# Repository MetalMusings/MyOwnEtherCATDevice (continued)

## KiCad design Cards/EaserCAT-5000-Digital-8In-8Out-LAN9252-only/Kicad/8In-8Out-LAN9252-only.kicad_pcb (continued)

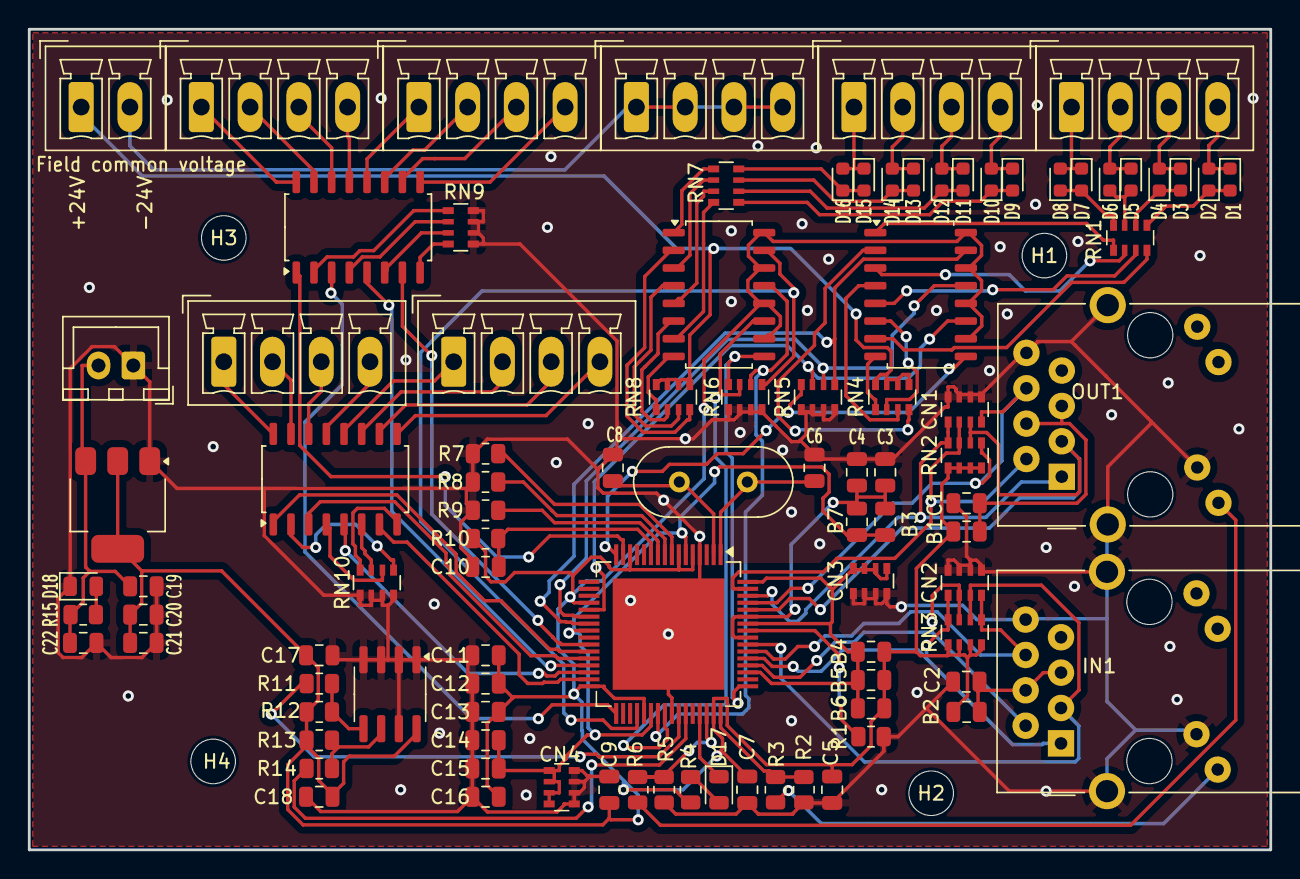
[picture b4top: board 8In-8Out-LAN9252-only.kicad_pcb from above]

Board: 2 copper layers, 89.2 x 58.9 mm, 99 parts (0 on the bottom side), 108 nets.

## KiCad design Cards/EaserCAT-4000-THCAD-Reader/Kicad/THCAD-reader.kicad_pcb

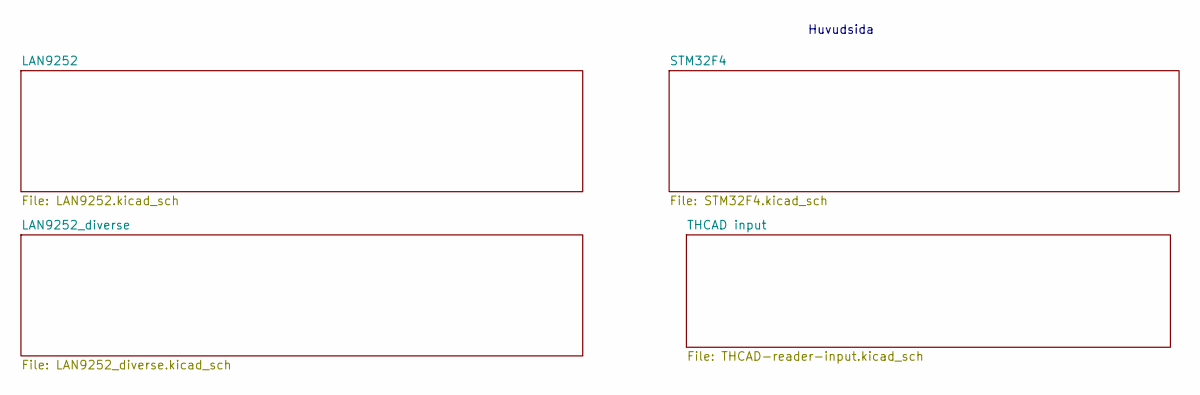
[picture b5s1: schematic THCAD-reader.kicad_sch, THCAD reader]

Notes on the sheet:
Huvudsida

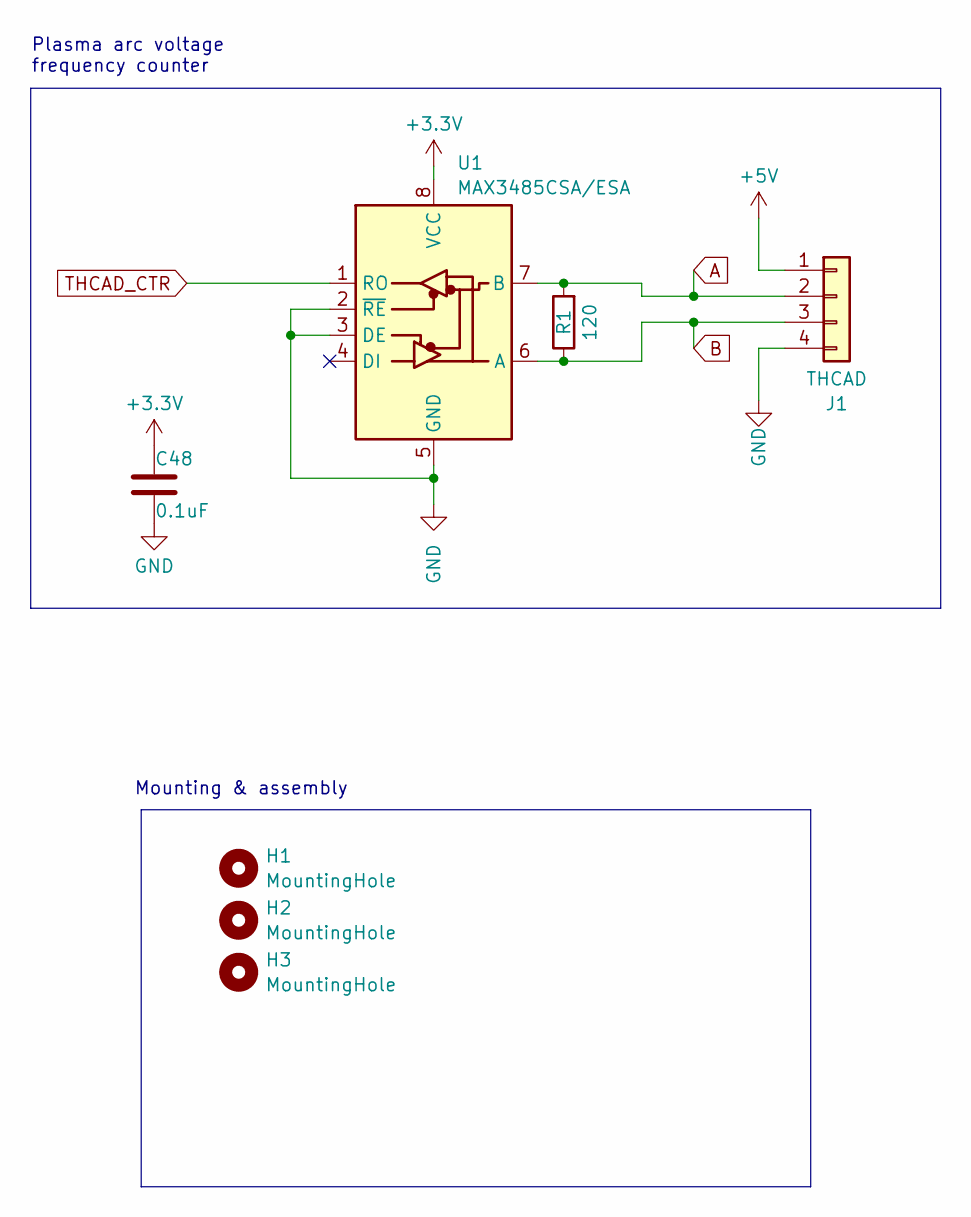
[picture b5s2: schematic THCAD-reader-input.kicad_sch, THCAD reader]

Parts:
C48: 0.1uF; C_0805_2012Metric
H1, H2, H3: MountingHole; MountingHole_3.2mm_M3
J1: THCAD; PhoenixContact_MCV_1,5_4-G-3.5_1x04_P3.50mm_Vertical
R1: 120; R_0805_2012Metric
U1: MAX3485CSA/ESA; SO-8_3.9x4.9mm_P1.27mm

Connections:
+3.3V: C48.1, U1.8 (VCC); also elsewhere on the board
+5V: J1.1; also elsewhere on the board
GND: C48.2, J1.4, U1.2 (~RE), U1.3 (DE), U1.5 (GND); also elsewhere on the board
unnamed: J1.2, R1.2, U1.7 (B)
unnamed: J1.3, R1.1, U1.6 (A)
THCAD_CTR: U1.1 (RO); also elsewhere on the board

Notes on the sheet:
Plasma arc voltage frequency counter
Mounting & assembly

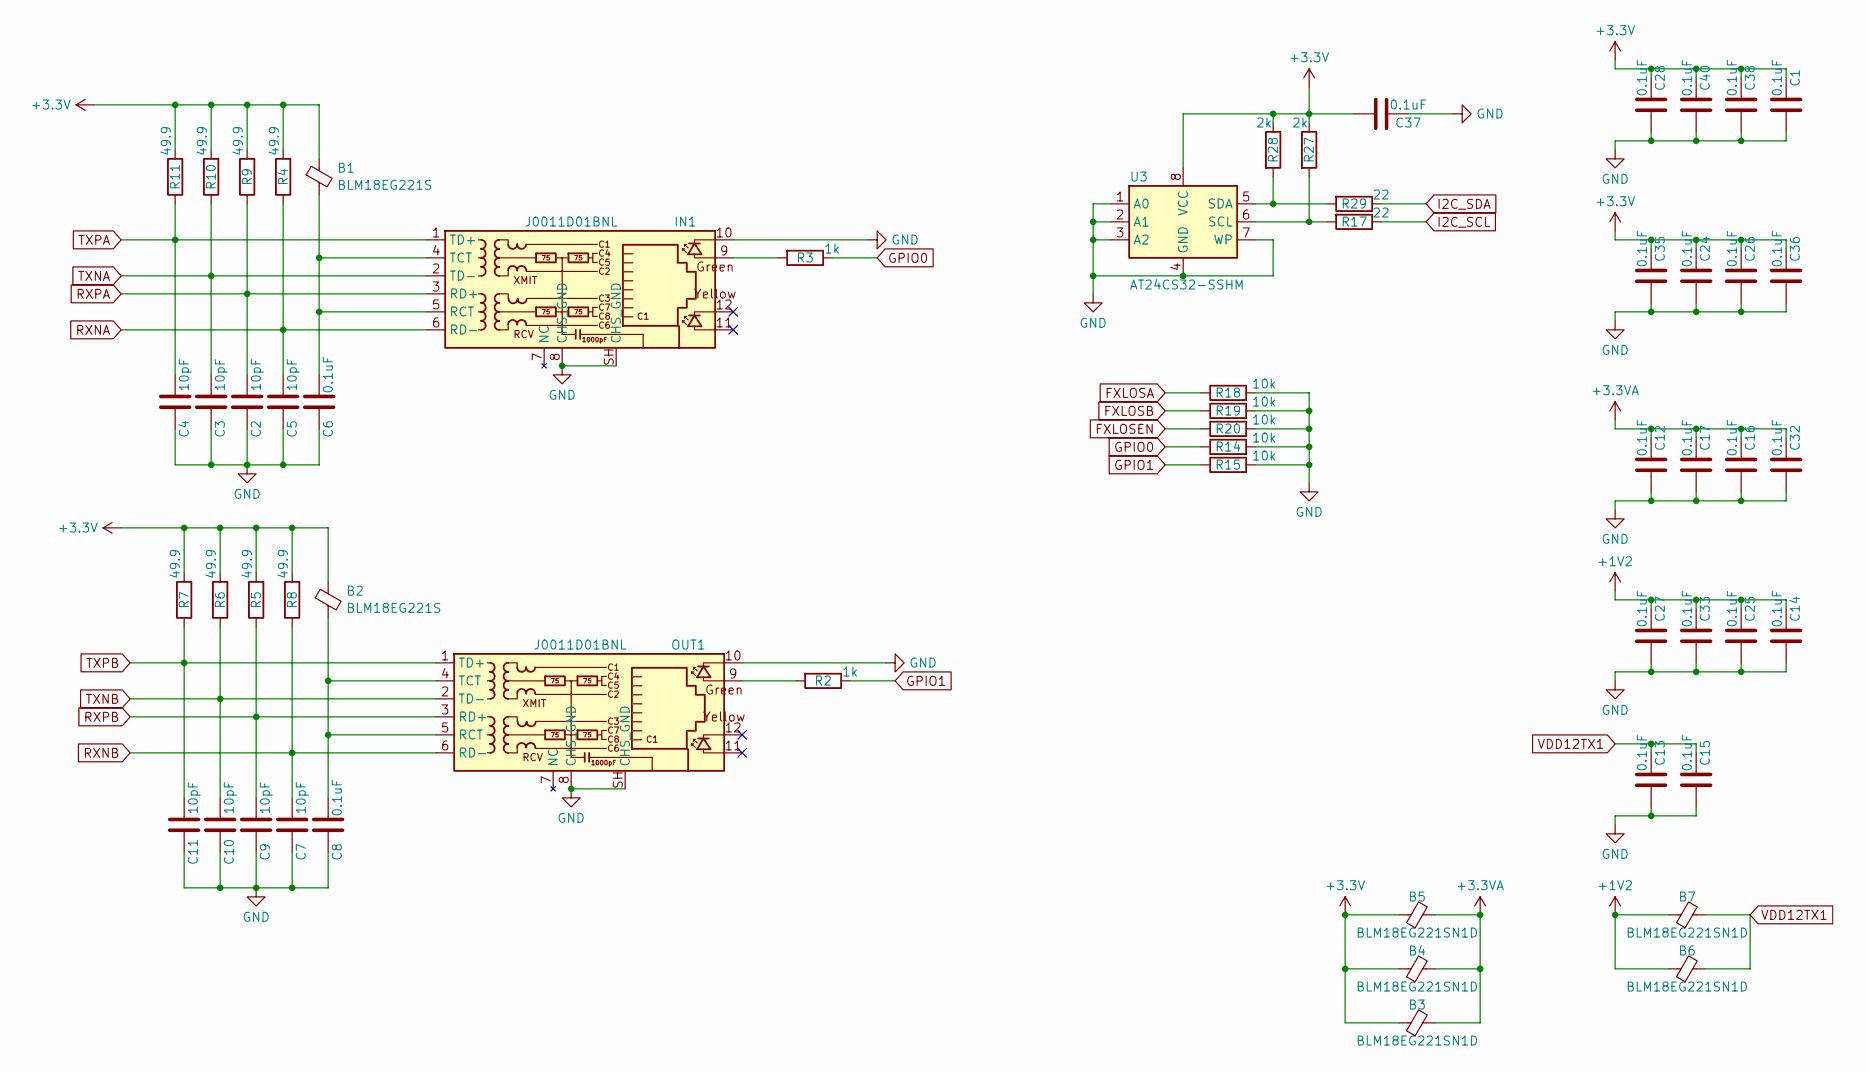
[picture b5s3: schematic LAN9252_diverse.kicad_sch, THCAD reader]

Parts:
B1, B2: BLM18EG221S; C_0805_2012Metric
B3, B4, B5, B6, B7: BLM18EG221SN1D; C_0805_2012Metric
C1, C6, C8, C12, C13, C14, C15, C16, C17, C24, C25, C26, C27, C28, C32, C33, C35, C36, C37, C38, C40: 0.1uF; C_0805_2012Metric
C2, C3, C4, C5, C7, C9, C10, C11: 10pF; C_0805_2012Metric
IN1: J0011D01BNL; PulseJack JB0011D01BNL
OUT1: J0011D01BNL; PulseJack JB0011D01BNL
R2, R3: 1k; R_0805_2012Metric
R4, R5, R6, R7, R8, R9, R10, R11: 49.9; R_0805_2012Metric
R14, R15, R18, R19, R20: 10k; R_0805_2012Metric
R17, R29: 22; R_0805_2012Metric
R27, R28: 2k; R_0805_2012Metric
U3: AT24CS32-SSHM; SOIC-8_3.9x4.9mm_P1.27mm

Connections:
+1V2: B6.1, B7.1, C14.1, C25.1, C27.1, C33.1; also elsewhere on the board
+3.3V: B1.1, B2.1, B3.1, B4.1, B5.1, C1.1, C24.1, C26.1, C28.1, C35.1, C36.1, C37.2, C38.1, C40.1, R4.2, R5.2, R6.2, R7.2, R8.2, R9.2, R10.2, R11.2, R27.1, R28.1, U3.8 (VCC); also elsewhere on the board
+3.3VA: B3.2, B4.2, B5.2, C12.1, C16.1, C17.1, C32.1; also elsewhere on the board
FXLOSA: R18.1; also elsewhere on the board
FXLOSB: R19.1; also elsewhere on the board
FXLOSEN: R20.1; also elsewhere on the board
GND: C1.2, C2.1, C3.1, C4.1, C5.1, C6.1, C7.1, C8.1, C9.1, C10.1, C11.1, C12.2, C13.2, C14.2, C15.2, C16.2, C17.2, C24.2, C25.2, C26.2, C27.2, C28.2, C32.2, C33.2, C35.2, C36.2, C37.1, C38.2, C40.2, IN1.8 (CHS_GND), IN1.10, IN1.SH (CHS_GND), OUT1.8 (CHS_GND), OUT1.10, OUT1.SH (CHS_GND), R14.2, R15.2, R18.2, R19.2, R20.2, U3.1 (A0), U3.2 (A1), U3.3 (A2), U3.4 (GND), U3.7 (WP); also elsewhere on the board
GPIO0: R3.1, R14.1; also elsewhere on the board
GPIO1: R2.1, R15.1; also elsewhere on the board
I2C_SCL: R17.1; also elsewhere on the board
I2C_SDA: R29.1; also elsewhere on the board
unnamed: IN1.9, R3.2
unnamed: B1.2, C6.2, IN1.4 (TCT), IN1.5 (RCT)
unnamed: OUT1.9, R2.2
unnamed: B2.2, C8.2, OUT1.4 (TCT), OUT1.5 (RCT)
unnamed: R17.2, R27.2, U3.6 (SCL)
unnamed: R28.2, R29.2, U3.5 (SDA)
RXNA: C5.2, IN1.6 (RD-), R4.1; also elsewhere on the board
RXNB: C7.2, OUT1.6 (RD-), R8.1; also elsewhere on the board
RXPA: C2.2, IN1.3 (RD+), R9.1; also elsewhere on the board
RXPB: C9.2, OUT1.3 (RD+), R5.1; also elsewhere on the board
TXNA: C3.2, IN1.2 (TD-), R10.1; also elsewhere on the board
TXNB: C10.2, OUT1.2 (TD-), R6.1; also elsewhere on the board
TXPA: C4.2, IN1.1 (TD+), R11.1; also elsewhere on the board
TXPB: C11.2, OUT1.1 (TD+), R7.1; also elsewhere on the board
VDD12TX1: B6.2, B7.2, C13.1, C15.1; also elsewhere on the board

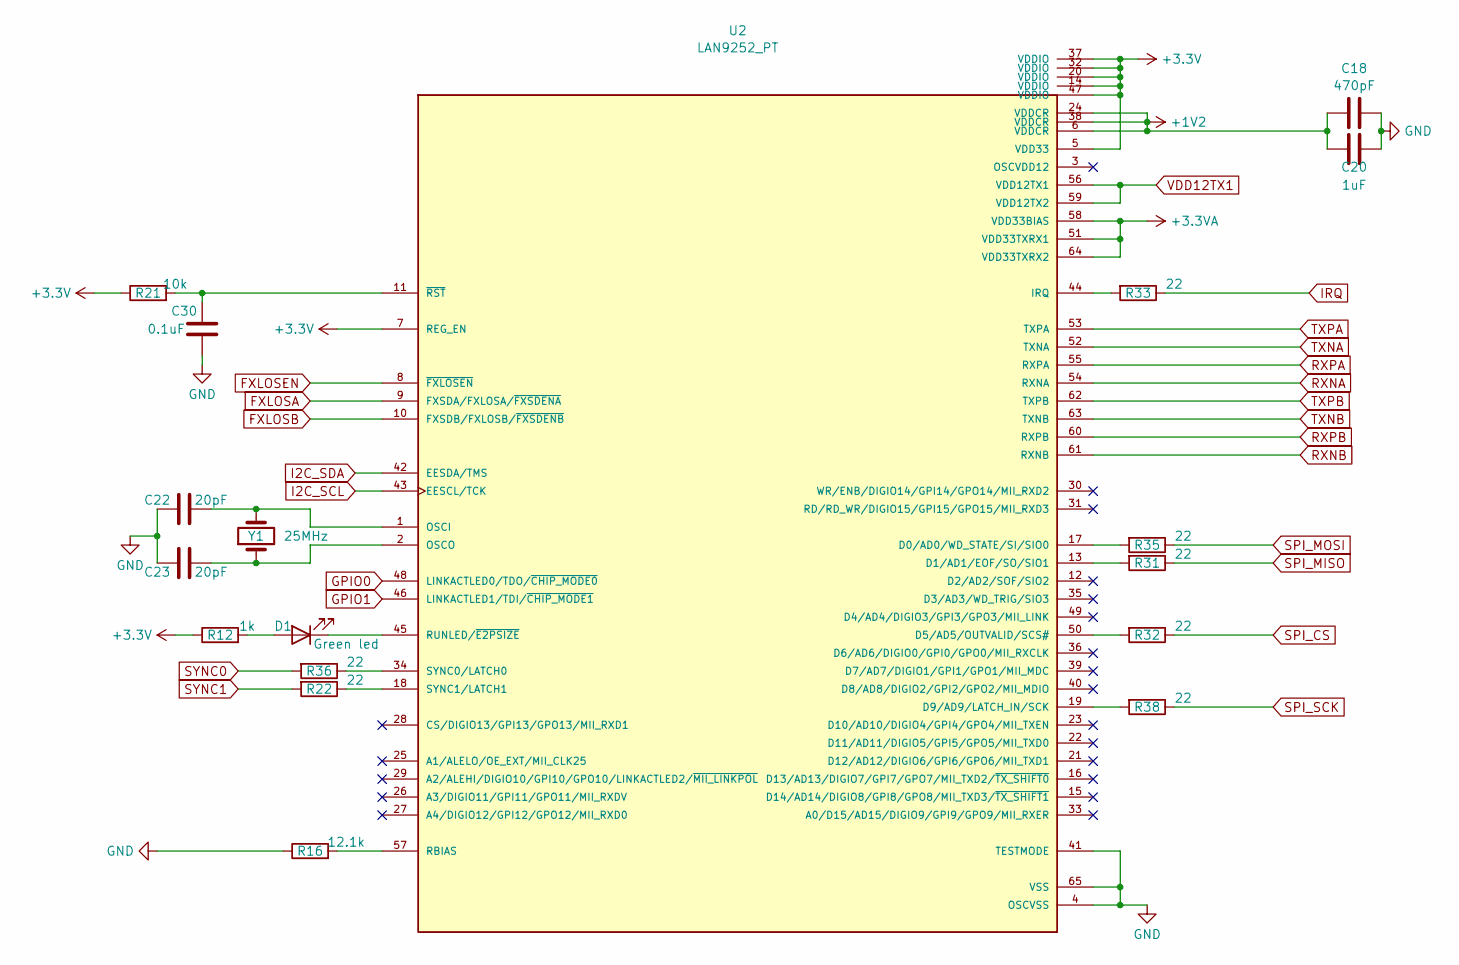
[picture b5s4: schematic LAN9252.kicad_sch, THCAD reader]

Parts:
C18: 470pF; C_0805_2012Metric
C20: 1uF; C_0805_2012Metric
C22, C23: 20pF; C_0805_2012Metric
C30: 0.1uF; C_0805_2012Metric
D1: Green led; LED_0805_2012Metric
R12: 1k; R_0805_2012Metric
R16: 12.1k; R_0805_2012Metric
R21: 10k; R_0805_2012Metric
R22, R31, R32, R33, R35, R36, R38: 22; R_0805_2012Metric
U2: LAN9252_PT; TQFP-64-1EP_10x10mm_P0.5mm_EP8x8mm; PARTREV 04-08-15
Y1: 25MHz; Crystal_HC49-4H_Vertical

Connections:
+1V2: C18.1, C20.1, U2.6 (VDDCR), U2.24 (VDDCR), U2.38 (VDDCR); also elsewhere on the board
+3.3V: R12.1, R21.1, U2.5 (VDD33), U2.7 (REG_EN), U2.14 (VDDIO), U2.20 (VDDIO), U2.32 (VDDIO), U2.37 (VDDIO), U2.47 (VDDIO); also elsewhere on the board
+3.3VA: U2.51 (VDD33TXRX1), U2.58 (VDD33BIAS), U2.64 (VDD33TXRX2); also elsewhere on the board
FXLOSA: U2.9 (FXSDA/FXLOSA/~FXSDENA); also elsewhere on the board
FXLOSB: U2.10 (FXSDB/FXLOSB/~FXSDENB); also elsewhere on the board
FXLOSEN: U2.8 (~FXLOSEN); also elsewhere on the board
GND: C18.2, C20.2, C22.1, C23.1, C30.1, R16.1, U2.4 (OSCVSS), U2.41 (TESTMODE), U2.65 (VSS); also elsewhere on the board
GPIO0: U2.48 (LINKACTLED0/TDO/~CHIP_MODE0); also elsewhere on the board
GPIO1: U2.46 (LINKACTLED1/TDI/~CHIP_MODE1); also elsewhere on the board
I2C_SCL: U2.43 (EESCL/TCK); also elsewhere on the board
I2C_SDA: U2.42 (EESDA/TMS); also elsewhere on the board
IRQ: R33.1; also elsewhere on the board
unnamed: D1.2 (A), R12.2
unnamed: D1.1 (K), U2.45 (RUNLED/~E2PSIZE)
unnamed: R35.2, U2.17 (D0/AD0/WD_STATE/SI/SIO0)
unnamed: R31.2, U2.13 (D1/AD1/EOF/SO/SIO1)
unnamed: R32.2, U2.50 (D5/AD5/OUTVALID/SCS#)
unnamed: R38.2, U2.19 (D9/AD9/LATCH_IN/SCK)
unnamed: R33.2, U2.44 (IRQ)
unnamed: C22.2, U2.1 (OSCI), Y1.2
unnamed: C23.2, U2.2 (OSCO), Y1.1
unnamed: R16.2, U2.57 (RBIAS)
unnamed: R36.1, U2.34 (SYNC0/LATCH0)
unnamed: R22.1, U2.18 (SYNC1/LATCH1)
unnamed: C30.2, R21.2, U2.11 (~RST)
RXNA: U2.54 (RXNA); also elsewhere on the board
RXNB: U2.61 (RXNB); also elsewhere on the board
RXPA: U2.55 (RXPA); also elsewhere on the board
RXPB: U2.60 (RXPB); also elsewhere on the board
SPI_CS: R32.1; also elsewhere on the board
SPI_MISO: R31.1; also elsewhere on the board
SPI_MOSI: R35.1; also elsewhere on the board
SPI_SCK: R38.1; also elsewhere on the board
SYNC0: R36.2; also elsewhere on the board
SYNC1: R22.2; also elsewhere on the board
TXNA: U2.52 (TXNA); also elsewhere on the board
TXNB: U2.63 (TXNB); also elsewhere on the board
TXPA: U2.53 (TXPA); also elsewhere on the board
TXPB: U2.62 (TXPB); also elsewhere on the board
VDD12TX1: U2.56 (VDD12TX1), U2.59 (VDD12TX2); also elsewhere on the board

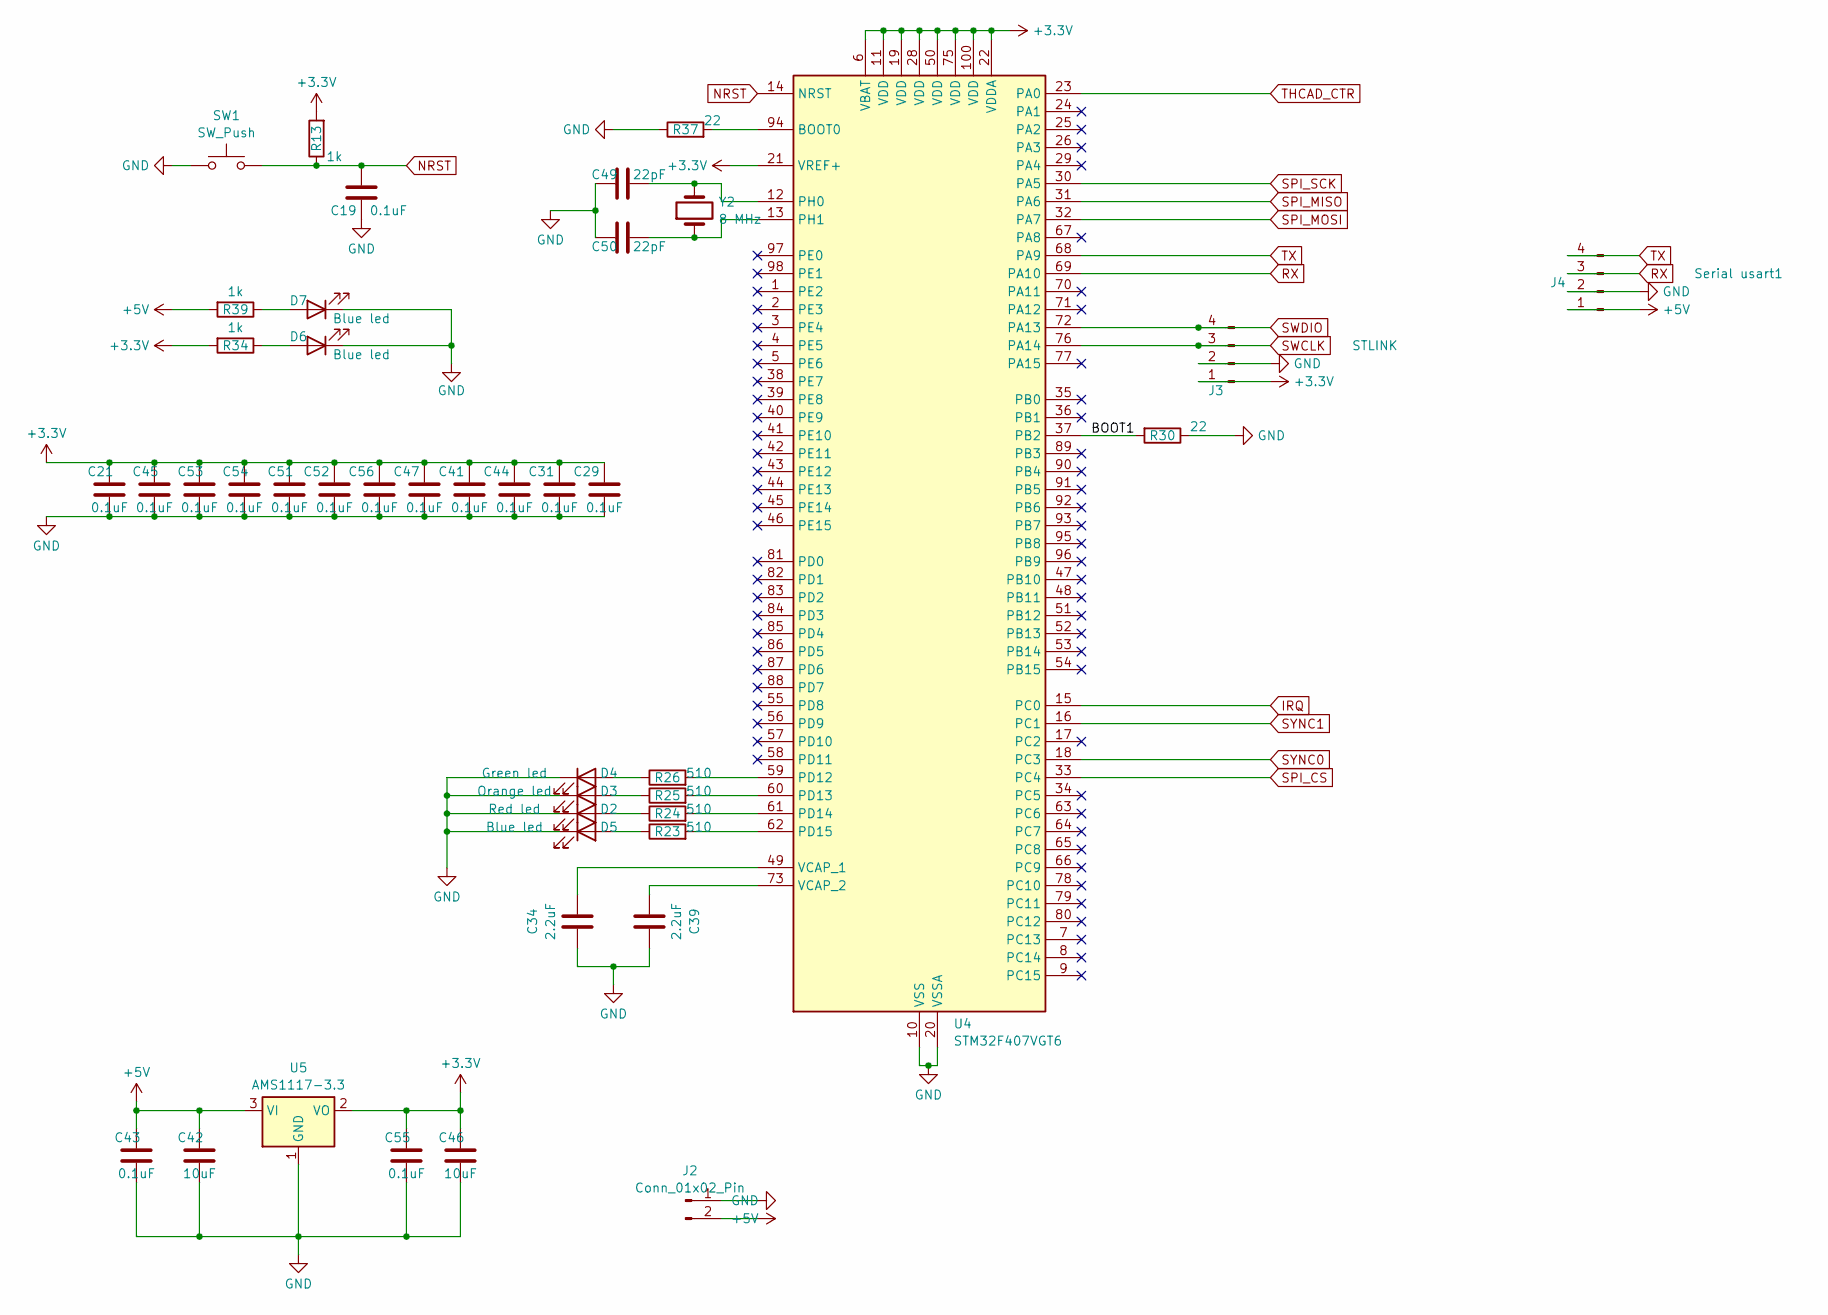
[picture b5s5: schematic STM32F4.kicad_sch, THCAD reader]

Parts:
C19, C21, C29, C31, C41, C43, C44, C45, C47, C51, C52, C53, C54, C55, C56: 0.1uF; C_0805_2012Metric
C34, C39: 2.2uF; C_0805_2012Metric
C42, C46: 10uF; C_0805_2012Metric
C49, C50: 22pF; C_0805_2012Metric
D2: Red led; LED_0805_2012Metric
D3: Orange led; LED_0805_2012Metric
D4: Green led; LED_0805_2012Metric
D5, D6, D7: Blue led; LED_0805_2012Metric
J2: Conn_01x02_Pin; JST_XH_B2B-XH-A_1x02_P2.50mm_Vertical
J3: STLINK; JST_XH_B4B-XH-A_1x04_P2.50mm_Vertical
J4: Serial usart1; JST_XH_B4B-XH-A_1x04_P2.50mm_Vertical
R13, R34, R39: 1k; R_0805_2012Metric
R23, R24, R25, R26: 510; R_0805_2012Metric
R30, R37: 22; R_0805_2012Metric
SW1: SW_Push; SW_Push_1P1T_XKB_TS-1187A
U4: STM32F407VGT6; LQFP-100_14x14mm_P0.5mm
U5: AMS1117-3.3; SOT-223-3_TabPin2
Y2: 8 MHz; Crystal_HC49-4H_Vertical

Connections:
+3.3V: C21.1, C29.1, C31.1, C41.1, C44.1, C45.1, C46.1, C47.1, C51.1, C52.1, C53.1, C54.1, C55.1, C56.1, J3.1, R13.2, R34.2, U4.6 (VBAT), U4.11 (VDD), U4.19 (VDD), U4.21 (VREF+), U4.22 (VDDA), U4.28 (VDD), U4.50 (VDD), U4.75 (VDD), U4.100 (VDD), U5.2 (VO); also elsewhere on the board
+5V: C42.1, C43.1, J2.2, J4.1, R39.2, U5.3 (VI); also elsewhere on the board
/STM32F4/BOOT1: R30.2, U4.37 (PB2)
GND: C19.1, C21.2, C29.2, C31.2, C34.1, C39.1, C41.2, C42.2, C43.2, C44.2, C45.2, C46.2, C47.2, C49.1, C50.1, C51.2, C52.2, C53.2, C54.2, C55.2, C56.2, D2.1 (K), D3.1 (K), D4.1 (K), D5.1 (K), D6.1 (K), D7.1 (K), J2.1, J3.2, J4.2, R30.1, R37.1, SW1.1, U4.10 (VSS), U4.20 (VSSA), U4.27 (VSS), U4.74 (VSS), U4.99 (VSS), U5.1 (GND); also elsewhere on the board
IRQ: U4.15 (PC0); also elsewhere on the board
NRST: C19.2, R13.1, SW1.2, U4.14 (NRST)
unnamed: D2.2 (A), R24.1
unnamed: D3.2 (A), R25.1
unnamed: D4.2 (A), R26.1
unnamed: D5.2 (A), R23.1
unnamed: D6.2 (A), R34.1
unnamed: D7.2 (A), R39.1
unnamed: R37.2, U4.94 (BOOT0)
unnamed: R26.2, U4.59 (PD12)
unnamed: R25.2, U4.60 (PD13)
unnamed: R24.2, U4.61 (PD14)
unnamed: R23.2, U4.62 (PD15)
unnamed: C49.2, U4.12 (PH0), Y2.2
unnamed: C50.2, U4.13 (PH1), Y2.1
unnamed: C34.2, U4.49 (VCAP_1)
unnamed: C39.2, U4.73 (VCAP_2)
RX: J4.3, U4.69 (PA10)
SPI_CS: U4.33 (PC4); also elsewhere on the board
SPI_MISO: U4.31 (PA6); also elsewhere on the board
SPI_MOSI: U4.32 (PA7); also elsewhere on the board
SPI_SCK: U4.30 (PA5); also elsewhere on the board
SWCLK: J3.3, U4.76 (PA14)
SWDIO: J3.4, U4.72 (PA13)
SYNC0: U4.18 (PC3); also elsewhere on the board
SYNC1: U4.16 (PC1); also elsewhere on the board
THCAD_CTR: U4.23 (PA0); also elsewhere on the board
TX: J4.4, U4.68 (PA9)

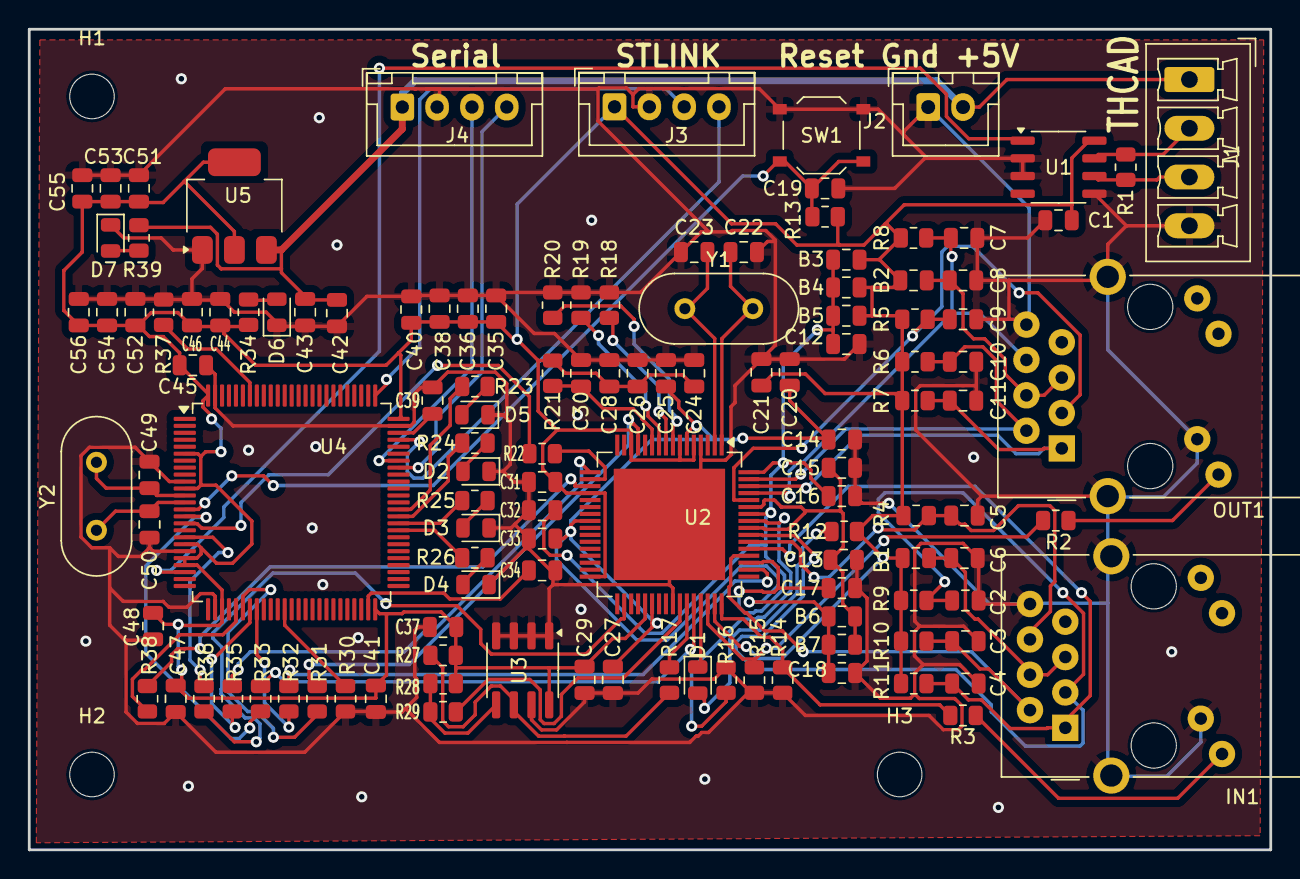
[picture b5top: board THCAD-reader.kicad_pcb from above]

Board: 2 copper layers, 89.2 x 58.9 mm, 126 parts (0 on the bottom side), 71 nets.

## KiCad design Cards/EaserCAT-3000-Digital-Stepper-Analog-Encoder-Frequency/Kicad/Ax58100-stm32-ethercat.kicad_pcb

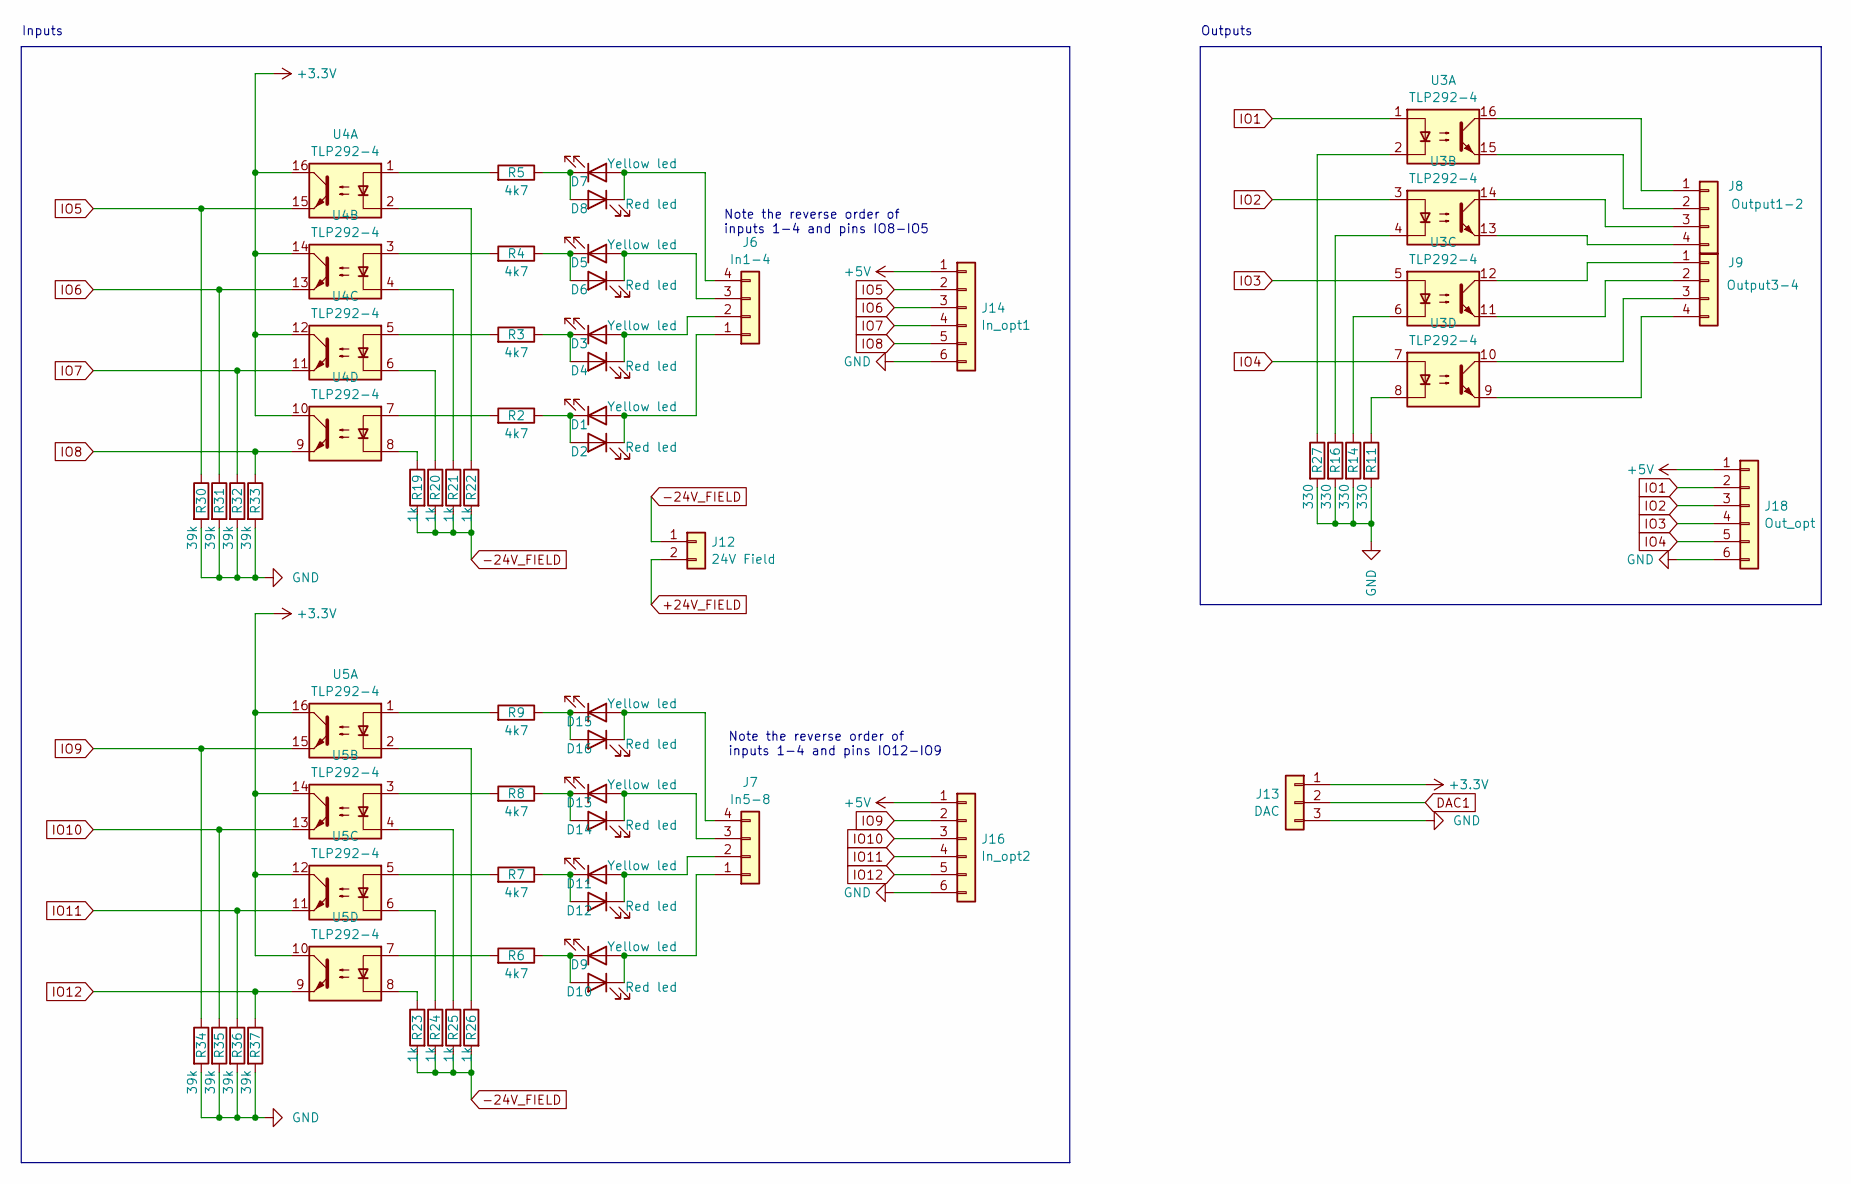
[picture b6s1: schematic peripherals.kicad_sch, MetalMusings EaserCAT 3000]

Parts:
D1, D3, D5, D7, D9, D11, D13, D15: Yellow led; LED_0603_1608Metric
D2, D4, D6, D8, D10, D12, D14, D16: Red led; LED_0603_1608Metric
J6: In1-4; PhoenixContact_MCV_1,5_4-G-3.5_1x04_P3.50mm_Vertical
J7: In5-8; PhoenixContact_MCV_1,5_4-G-3.5_1x04_P3.50mm_Vertical
J8: Output1-2; PhoenixContact_MCV_1,5_4-G-3.5_1x04_P3.50mm_Vertical
J9: Output3-4; PhoenixContact_MCV_1,5_4-G-3.5_1x04_P3.50mm_Vertical
J12: 24V Field; PhoenixContact_MCV_1,5_2-G-3.5_1x02_P3.50mm_Vertical
J13: DAC; PhoenixContact_MCV_1,5_3-G-3.5_1x03_P3.50mm_Vertical
J14: In_opt1; JST_XH_B6B-XH-A_1x06_P2.50mm_Vertical
J16: In_opt2; JST_XH_B6B-XH-A_1x06_P2.50mm_Vertical
J18: Out_opt; JST_XH_B6B-XH-A_1x06_P2.50mm_Vertical
R2, R3, R4, R5, R6, R7, R8, R9: 4k7; R_0603_1608Metric
R11, R14, R16, R27: 330; R_0603_1608Metric
R19, R20, R21, R22, R23, R24, R25, R26: 1k; R_0603_1608Metric
R30, R31, R32, R33, R34, R35, R36, R37: 39k; R_0603_1608Metric
U3, U4, U5: TLP292-4; SOIC-16_4.55x10.3mm_P1.27mm

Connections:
+3.3V: J13.1, U4.10, U4.12, U4.14, U4.16, U5.10, U5.12, U5.14, U5.16; also elsewhere on the board
+5V: J14.1, J16.1, J18.1; also elsewhere on the board
+24V_FIELD: J12.2
-24V_FIELD: J12.1, R19.2, R20.2, R21.2, R22.2, R23.2, R24.2, R25.2, R26.2
DAC1: J13.2; also elsewhere on the board
GND: J13.3, J14.6, J16.6, J18.6, R11.2, R14.2, R16.2, R27.2, R30.2, R31.2, R32.2, R33.2, R34.2, R35.2, R36.2, R37.2; also elsewhere on the board
IO1: J18.2, U3.1; also elsewhere on the board
IO2: J18.3, U3.3; also elsewhere on the board
IO3: J18.4, U3.5; also elsewhere on the board
IO4: J18.5, U3.7; also elsewhere on the board
IO5: J14.2, R30.1, U4.15; also elsewhere on the board
IO6: J14.3, R31.1, U4.13; also elsewhere on the board
IO7: J14.4, R32.1, U4.11; also elsewhere on the board
IO8: J14.5, R33.1, U4.9; also elsewhere on the board
IO9: J16.2, R34.1, U5.15; also elsewhere on the board
IO10: J16.3, R35.1, U5.13; also elsewhere on the board
IO11: J16.4, R36.1, U5.11; also elsewhere on the board
IO12: J16.5, R37.1, U5.9; also elsewhere on the board
unnamed: D1.2 (A), D2.1 (K), J6.1
unnamed: D1.1 (K), D2.2 (A), R2.1
unnamed: D3.2 (A), D4.1 (K), J6.2
unnamed: D3.1 (K), D4.2 (A), R3.1
unnamed: D5.2 (A), D6.1 (K), J6.3
unnamed: D5.1 (K), D6.2 (A), R4.1
unnamed: D7.2 (A), D8.1 (K), J6.4
unnamed: D7.1 (K), D8.2 (A), R5.1
unnamed: D9.1 (K), D10.2 (A), R6.1
unnamed: D9.2 (A), D10.1 (K), J7.1
unnamed: D11.2 (A), D12.1 (K), J7.2
unnamed: D11.1 (K), D12.2 (A), R7.1
unnamed: D13.2 (A), D14.1 (K), J7.3
unnamed: D13.1 (K), D14.2 (A), R8.1
unnamed: D15.2 (A), D16.1 (K), J7.4
unnamed: D15.1 (K), D16.2 (A), R9.1
unnamed: J8.1, U3.16
unnamed: J8.2, U3.15
unnamed: J8.3, U3.14
unnamed: J8.4, U3.13
unnamed: J9.1, U3.12
unnamed: J9.2, U3.11
unnamed: J9.3, U3.10
unnamed: J9.4, U3.9
unnamed: R2.2, U4.7
unnamed: R3.2, U4.5
unnamed: R4.2, U4.3
unnamed: R5.2, U4.1
unnamed: R6.2, U5.7
unnamed: R7.2, U5.5
unnamed: R8.2, U5.3
unnamed: R9.2, U5.1
unnamed: R11.1, U3.8
unnamed: R14.1, U3.6
unnamed: R16.1, U3.4
unnamed: R19.1, U4.8
unnamed: R20.1, U4.6
unnamed: R21.1, U4.4
unnamed: R22.1, U4.2
unnamed: R23.1, U5.8
unnamed: R24.1, U5.6
unnamed: R25.1, U5.4
unnamed: R26.1, U5.2
unnamed: R27.1, U3.2

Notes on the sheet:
Inputs
Note the reverse order of inputs 1-4 and pins IO12-IO9
Note the reverse order of inputs 1-4 and pins IO8-IO5
Outputs

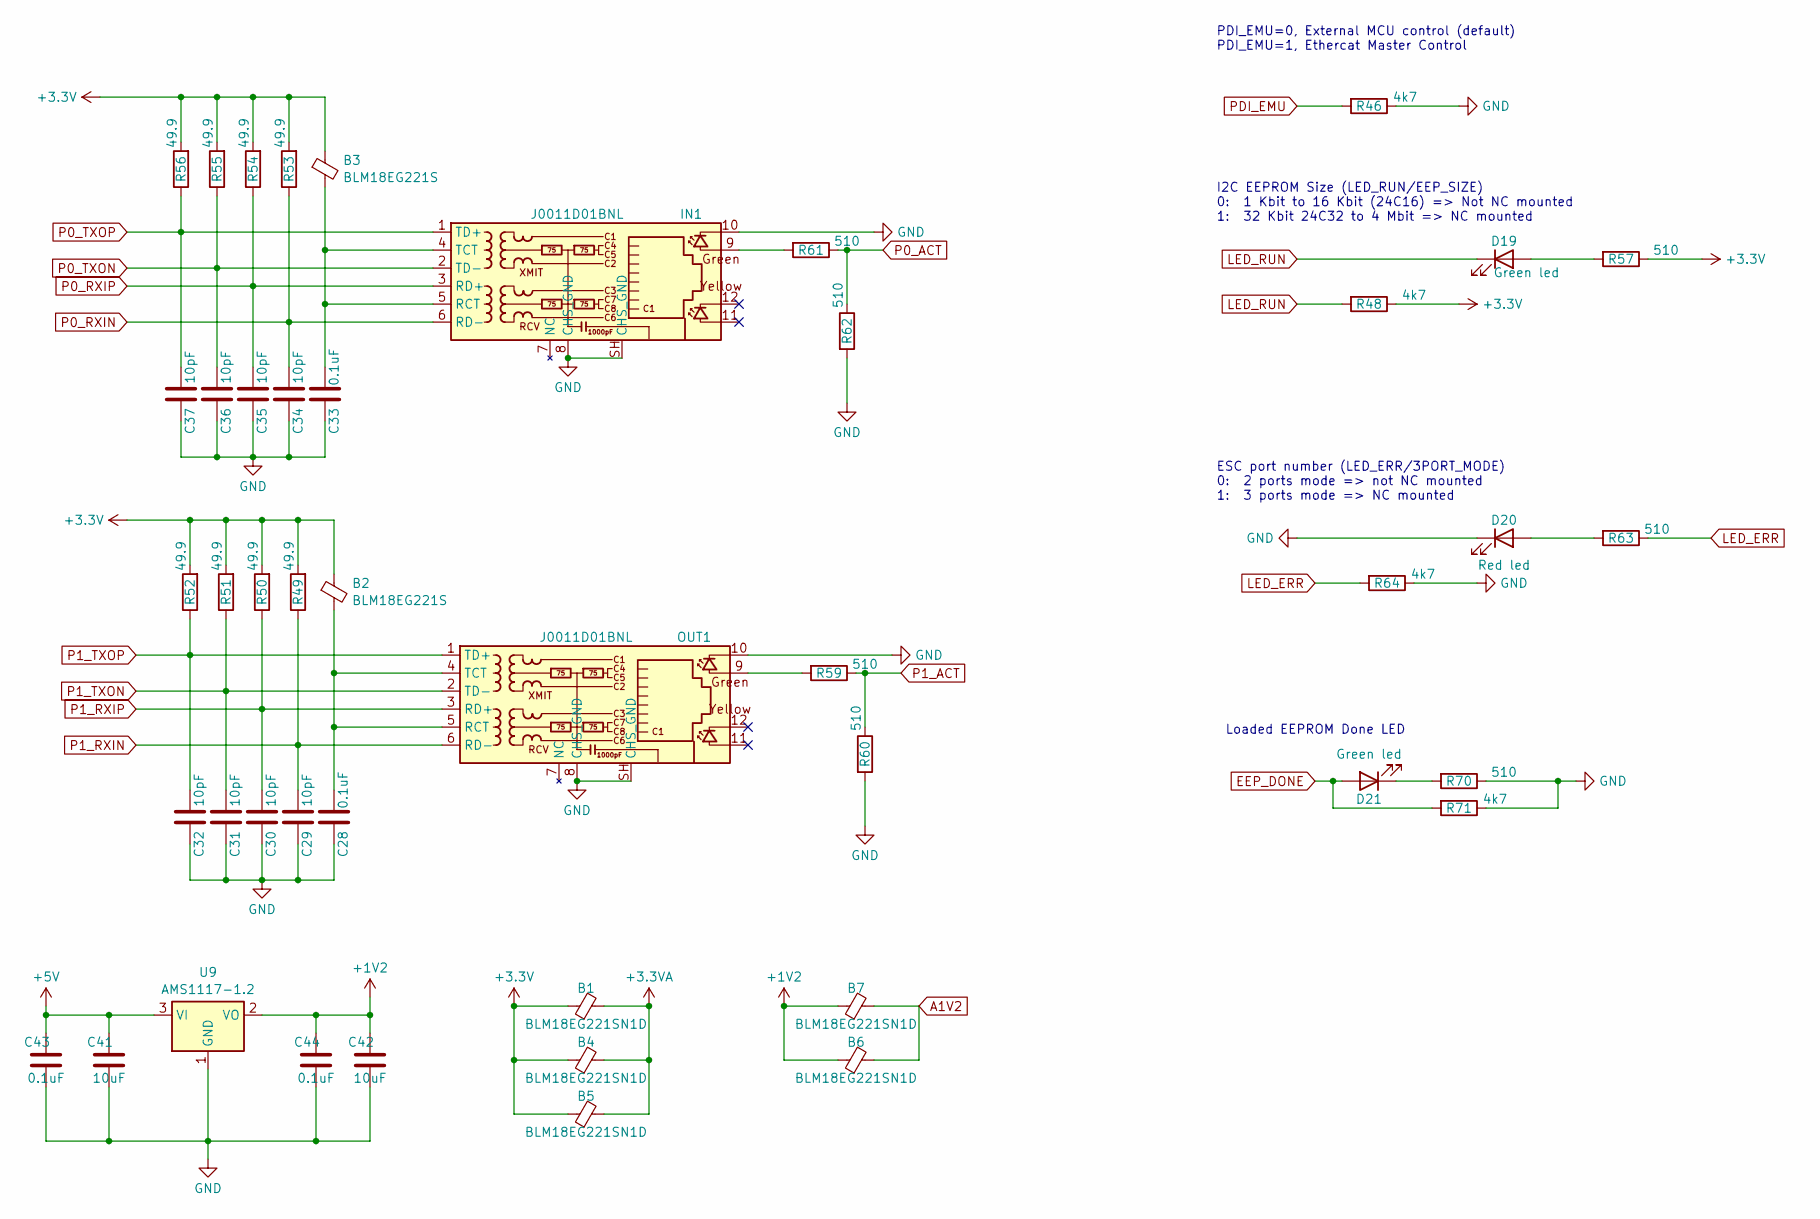
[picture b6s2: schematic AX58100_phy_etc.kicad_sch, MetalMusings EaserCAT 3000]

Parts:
B1, B4, B5, B6, B7: BLM18EG221SN1D; C_0805_2012Metric
B2, B3: BLM18EG221S; C_0805_2012Metric
C28, C33, C43, C44: 0.1uF; C_0805_2012Metric
C29, C30, C31, C32, C34, C35, C36, C37: 10pF; C_0805_2012Metric
C41, C42: 10uF; C_0805_2012Metric
D19, D21: Green led; LED_0603_1608Metric
D20: Red led; LED_0603_1608Metric
IN1: J0011D01BNL; PulseJack JB0011D01BNL
OUT1: J0011D01BNL; PulseJack JB0011D01BNL
R46, R48, R64, R71: 4k7; R_0805_2012Metric
R49, R50, R51, R52, R53, R54, R55, R56: 49.9; R_0805_2012Metric
R57, R59, R60, R61, R62, R63, R70: 510; R_0805_2012Metric
U9: AMS1117-1.2; SOT-223-3_TabPin2

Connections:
+1V2: B6.1, B7.1, C42.1, C44.1, U9.2 (VO); also elsewhere on the board
+3.3V: B1.1, B2.1, B3.1, B4.1, B5.1, R48.1, R49.2, R50.2, R51.2, R52.2, R53.2, R54.2, R55.2, R56.2, R57.1; also elsewhere on the board
+3.3VA: B1.2, B4.2, B5.2; also elsewhere on the board
+5V: C41.1, C43.1, U9.3 (VI); also elsewhere on the board
A1V2: B6.2, B7.2; also elsewhere on the board
EEP_DONE: D21.2 (A), R71.2; also elsewhere on the board
GND: C28.1, C29.1, C30.1, C31.1, C32.1, C33.1, C34.1, C35.1, C36.1, C37.1, C41.2, C42.2, C43.2, C44.2, D20.1 (K), IN1.8 (CHS_GND), IN1.10, IN1.SH (CHS_GND), OUT1.8 (CHS_GND), OUT1.10, OUT1.SH (CHS_GND), R46.1, R60.2, R62.2, R64.1, R70.1, R71.1, U9.1 (GND); also elsewhere on the board
LED_ERR: R63.1, R64.2; also elsewhere on the board
LED_RUN: D19.1 (K), R48.2; also elsewhere on the board
unnamed: D19.2 (A), R57.2
unnamed: D20.2 (A), R63.2
unnamed: D21.1 (K), R70.2
unnamed: IN1.9, R61.2
unnamed: B3.2, C33.2, IN1.4 (TCT), IN1.5 (RCT)
unnamed: OUT1.9, R59.2
unnamed: B2.2, C28.2, OUT1.4 (TCT), OUT1.5 (RCT)
P0_ACT: R61.1, R62.1; also elsewhere on the board
P0_RXIN: C34.2, IN1.6 (RD-), R53.1; also elsewhere on the board
P0_RXIP: C35.2, IN1.3 (RD+), R54.1; also elsewhere on the board
P0_TXON: C36.2, IN1.2 (TD-), R55.1; also elsewhere on the board
P0_TXOP: C37.2, IN1.1 (TD+), R56.1; also elsewhere on the board
P1_ACT: R59.1, R60.1; also elsewhere on the board
P1_RXIN: C29.2, OUT1.6 (RD-), R49.1; also elsewhere on the board
P1_RXIP: C30.2, OUT1.3 (RD+), R50.1; also elsewhere on the board
P1_TXON: C31.2, OUT1.2 (TD-), R51.1; also elsewhere on the board
P1_TXOP: C32.2, OUT1.1 (TD+), R52.1; also elsewhere on the board
PDI_EMU: R46.2; also elsewhere on the board

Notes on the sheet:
PDI_EMU=0, External MCU control (default) PDI_EMU=1, Ethercat Master Control
I2C EEPROM Size (LED_RUN/EEP_SIZE) 0: 1 Kbit to 16 Kbit (24C16) => Not NC mounted 1: 32 Kbit 24C32 to 4 Mbit => NC mounted
ESC port number (LED_ERR/3PORT_MODE) 0: 2 ports mode => not NC mounted 1: 3 ports mode => NC mounted
Loaded EEPROM Done LED
